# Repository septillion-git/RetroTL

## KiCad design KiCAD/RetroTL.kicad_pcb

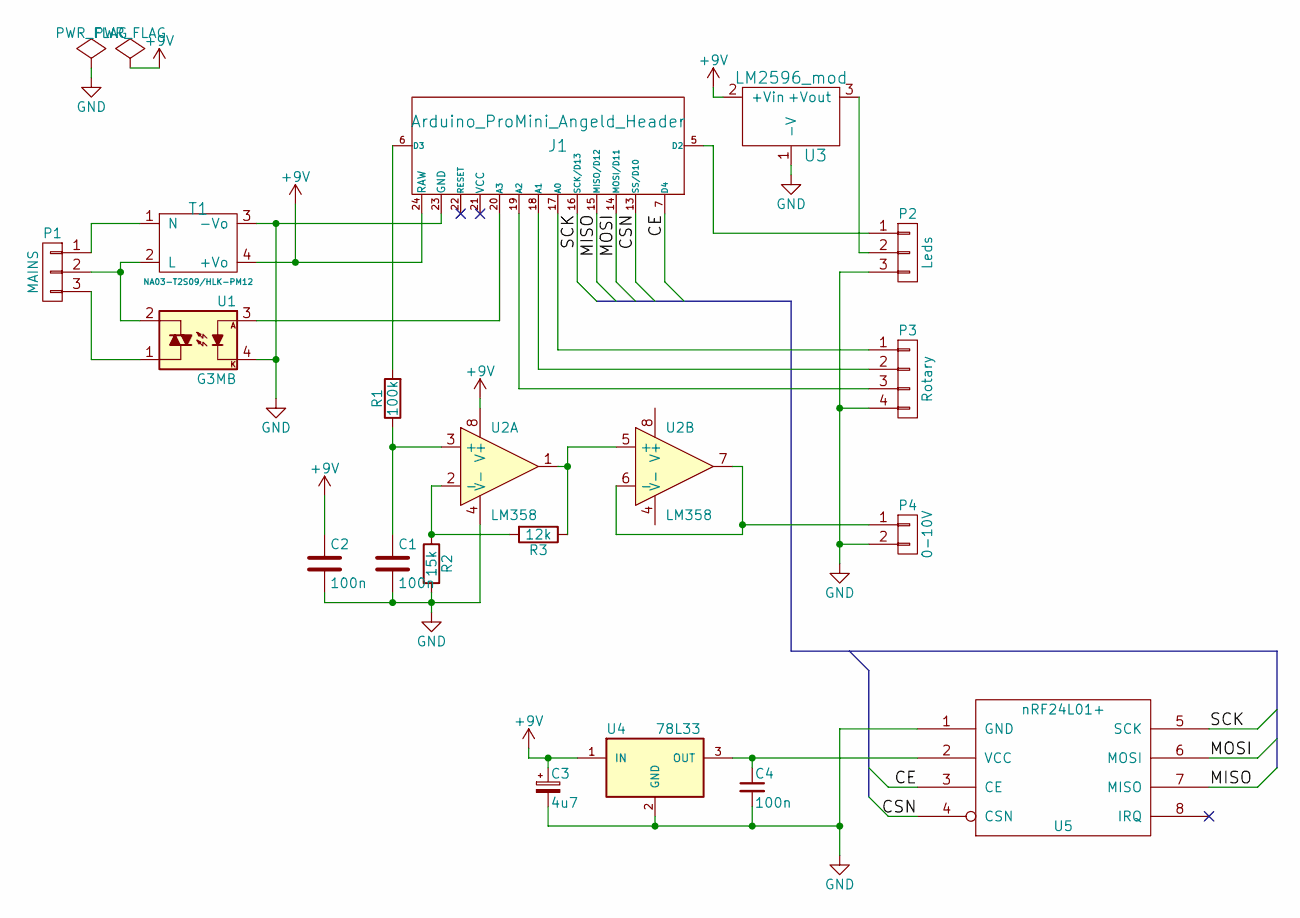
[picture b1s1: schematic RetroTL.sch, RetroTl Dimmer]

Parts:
C1, C2, C4: 100n; C_0805_HandSoldering
C3: 4u7; C_Radial_D5_L6_P2.5
J1: Arduino_ProMini_Angeld_Header; Arduino_ProMini_Angeled_Small++
P1: MAINS; bornier3
P2: Leds; pin_strip_3
P3: Rotary; pin_strip_4
P4: 0-10V; pin_strip_2
R1: 100k; R_0805_HandSoldering
R2: 15k; R_0805_HandSoldering
R3: 12k; R_0805_HandSoldering
T1: NA03-T2S09/HLK-PM12; Universal_NA03-T2Sxx_HLK-PMxx
U1: G3MB; G3MB-xxxx
U2: LM358; SOIC-8-N
U3: LM2596_mod; MP2307_module_3pin
U4: 78L33; TO-92_Inline_Narrow_Oval
U5: nRF24L01+; NRF24L01_MODULE

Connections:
+9V: C2.1, C3.1, J1.24 (RAW), T1.4 (+Vo), U2.8 (V+), U3.2 (+Vin), U4.1 (IN)
/CE: J1.7 (D4), U5.3 (CE)
/CSN: J1.13 (SS/D10), U5.4 (CSN)
/MISO: J1.15 (MISO/D12), U5.7 (MISO)
/MOSI: J1.14 (MOSI/D11), U5.6 (MOSI)
/SCK: J1.16 (SCK/D13), U5.5 (SCK)
GND: C1.2, C2.2, C3.2, C4.2, J1.23 (GND), P2.3, P3.4, P4.2, R2.2, T1.3 (-Vo), U1.4, U2.4 (V-), U3.1 (-V), U4.2 (GND), U5.1 (GND)
unnamed: C1.1, R1.1, U2.3 (+)
unnamed: C4.1, U4.3 (OUT), U5.2 (VCC)
unnamed: J1.5 (D2), P2.1
unnamed: J1.6 (D3), R1.2
unnamed: J1.17 (A0), P3.1
unnamed: J1.18 (A1), P3.2
unnamed: J1.19 (A2), P3.3
unnamed: J1.20 (A3), U1.3
unnamed: P1.1, T1.1 (N)
unnamed: P1.2, T1.2 (L), U1.2
unnamed: P1.3, U1.1
unnamed: P2.2, U3.3 (+Vout)
unnamed: P4.1, U2.6 (-), U2.7
unnamed: R2.1, R3.2, U2.2 (-)
unnamed: R3.1, U2.1, U2.5 (+)

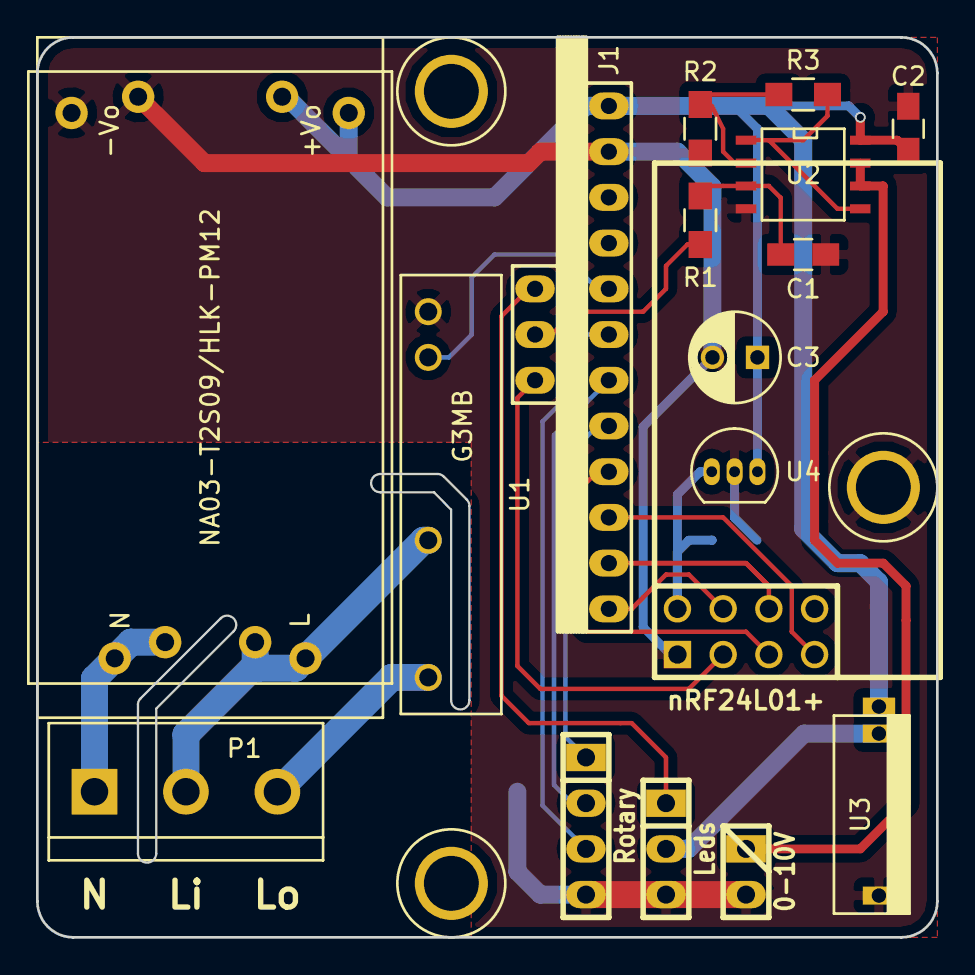
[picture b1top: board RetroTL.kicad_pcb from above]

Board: 2 copper layers, 50.0 x 50.0 mm, 18 parts (1 on the bottom side), 22 nets.

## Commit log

2016-09-05 :circus_tent: Added .gitattributes & .gitignore files
2016-09-05 First publish
    incl PCB based on RF433
2016-09-05 Schematic change to RF34L01
2016-09-08 PCB with NRF24N01
2016-09-08 Small fixes
2016-09-08 Added DirtyPCBs Gerbers
2016-09-09 Added some schematic values
2016-10-11 Added first test code
2016-10-24 Now turns on and off
2016-12-01 Added Gamma correction
